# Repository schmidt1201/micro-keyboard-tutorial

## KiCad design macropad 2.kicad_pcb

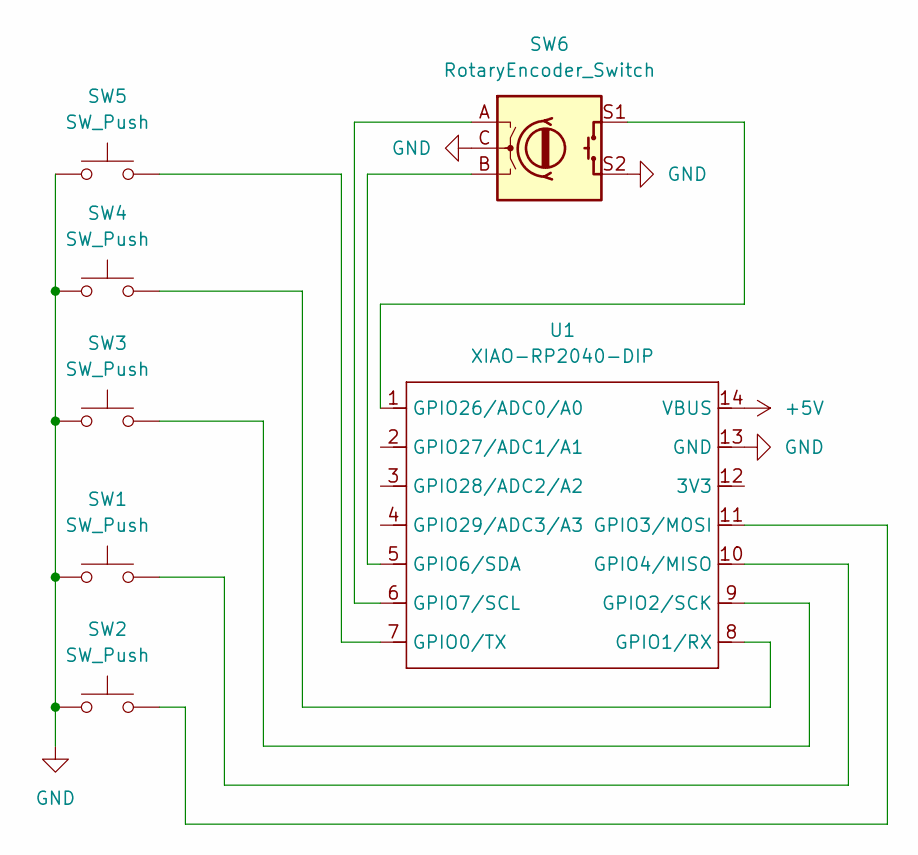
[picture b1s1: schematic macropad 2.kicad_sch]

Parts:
SW1, SW2, SW3, SW4, SW5: SW_Push; SW_Cherry_MX_1.00u_PCB
SW6: RotaryEncoder_Switch; RotaryEncoder_Alps_EC11E-Switch_Vertical_H20mm
U1: XIAO-RP2040-DIP

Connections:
+5V: U1.14 (VBUS)
GND: SW1.1, SW2.2, SW3.1, SW4.1, SW5.1, SW6.C, SW6.S2, U1.13 (GND)
unnamed: SW5.2, U1.7 (GPIO0/TX)
unnamed: SW4.2, U1.8 (GPIO1/RX)
unnamed: SW3.2, U1.9 (GPIO2/SCK)
unnamed: SW2.1, U1.11 (GPIO3/MOSI)
unnamed: SW1.2, U1.10 (GPIO4/MISO)
unnamed: SW6.B, U1.5 (GPIO6/SDA)
unnamed: SW6.A, U1.6 (GPIO7/SCL)
unnamed: SW6.S1, U1.1 (GPIO26/ADC0/A0)

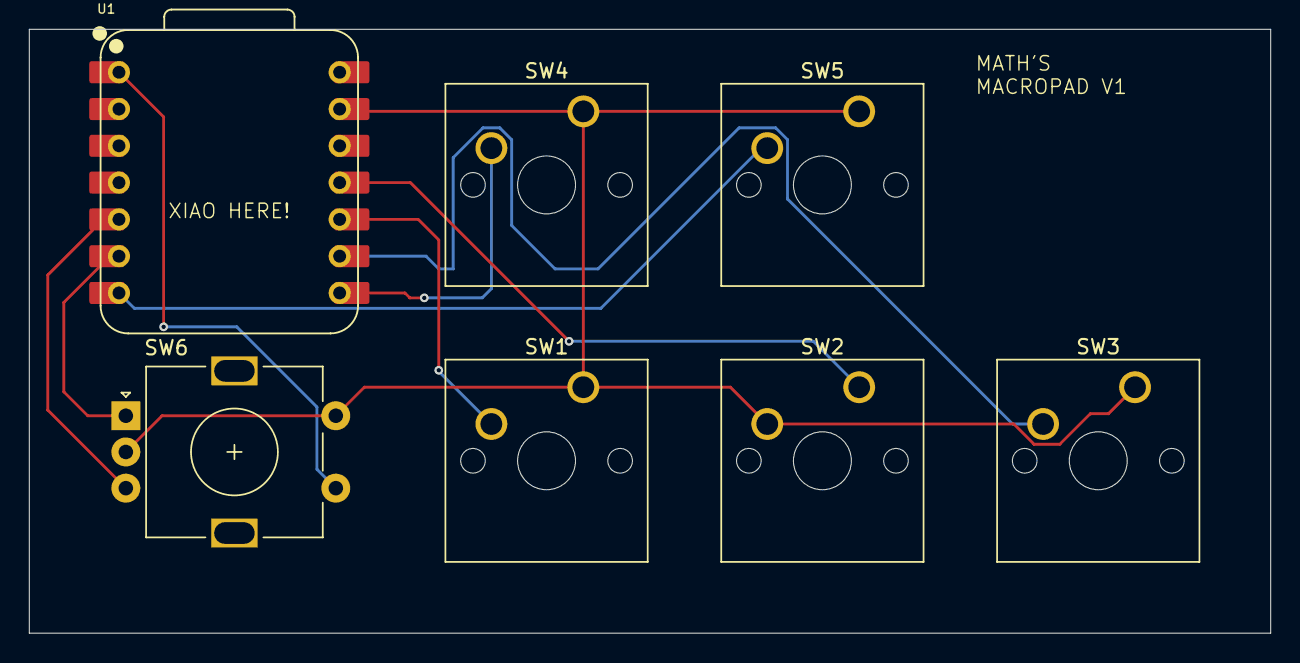
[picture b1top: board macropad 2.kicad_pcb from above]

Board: 2 copper layers, 85.7 x 41.7 mm, 7 parts (0 on the bottom side), 9 nets.

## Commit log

2026-01-03 added schematic todo: assign footprints
    added initial schematic with 5 switches and 1 encoder
2026-01-03 added footprints
    added footprints to 5 switches, encoder and rp2040
2026-01-04 PCB added
    v1 pcb (wired)
